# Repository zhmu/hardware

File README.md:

# hardware

Collection of various hardware projects

## avr-ldr

Simple PCB with an ATTiny2313 and PCA82C250 CAN <-> TTL transceiver to be able to monitor an energy meter's power LED.

## c64-psu

Commodore 64 power supply unit, intended to be safer, more reliable and more efficient than the original.

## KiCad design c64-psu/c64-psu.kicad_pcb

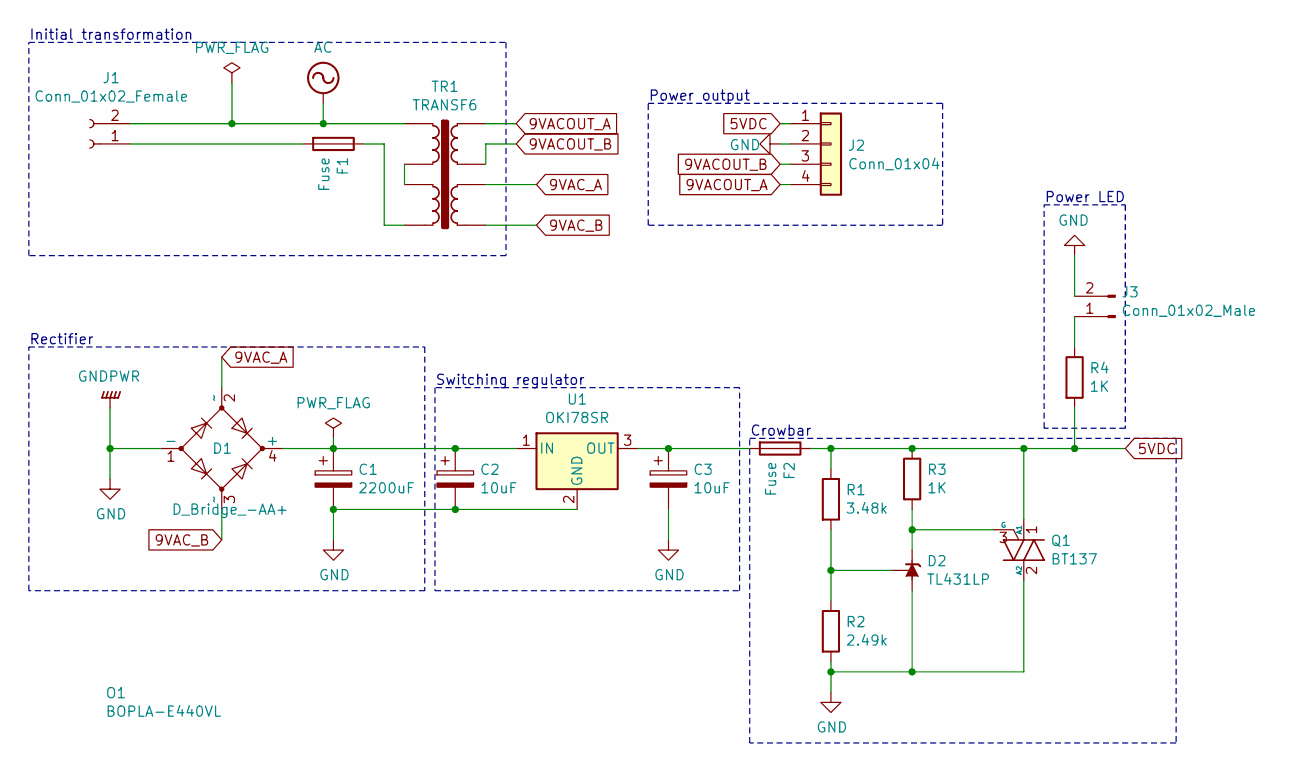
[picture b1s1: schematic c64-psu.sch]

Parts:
C1: 2200uF; CP_Radial_D13.0mm_P5.00mm
C2, C3: 10uF; CP_Radial_D5.0mm_P2.00mm
D1: D_Bridge_-AA+; Diode_Bridge_Vishay_KBU
D2: TL431LP; TO-92_HandSolder
F1, F2: Fuse; Fuseholder_Cylinder-5x20mm_Schurter_0031_8201_Horizontal_Op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
J1: Conn_01x02_Female; RND00023
J2: Conn_01x04; Molex_KK-396_A-41791-0004_1x04_P3.96mm_Vertical
J3: Conn_01x02_Male; Molex_KK-254_AE-6410-02A_1x02_P2.54mm_Vertical
O1: BOPLA-E440VL; BOPLA_E440VL
Q1: BT137; TO-220-3_Vertical
R1: 3.48k; R_Axial_DIN0207_L6.3mm_D2.5mm_P10.16mm_Horizontal
R2: 2.49k; R_Axial_DIN0207_L6.3mm_D2.5mm_P10.16mm_Horizontal
R3, R4: 1K; R_Axial_DIN0207_L6.3mm_D2.5mm_P10.16mm_Horizontal
TR1: TRANSF6; Transformer-FL30
U1: OKI78SR; TO-220-3_Vertical

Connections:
5VDC: F2.1, J2.1, Q1.1 (A1), R1.1, R3.1, R4.2
9VACOUT_A: J2.4, TR1.8
9VACOUT_B: J2.3, TR1.7
9VAC_A: D1.2 (~~), TR1.6
9VAC_B: D1.3 (~~), TR1.5
AC: J1.2, TR1.1
GND: C1.2, C2.2, C3.2, D1.1 (-), D2.2 (A), J2.2, J3.2, Q1.2 (A2), R2.2, U1.2 (GND)
unnamed: C1.1, C2.1, D1.4 (+), U1.1 (IN)
unnamed: C3.1, F2.2, U1.3 (OUT)
unnamed: D2.1 (REF), R1.2, R2.1
unnamed: D2.3 (K), Q1.3 (G), R3.2
unnamed: F1.1, TR1.4
unnamed: F1.2, J1.1
unnamed: J3.1, R4.1
unnamed: TR1.2, TR1.3

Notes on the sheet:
Initial transformation
Power output
Rectifier
Switching regulator
Crowbar
Power LED

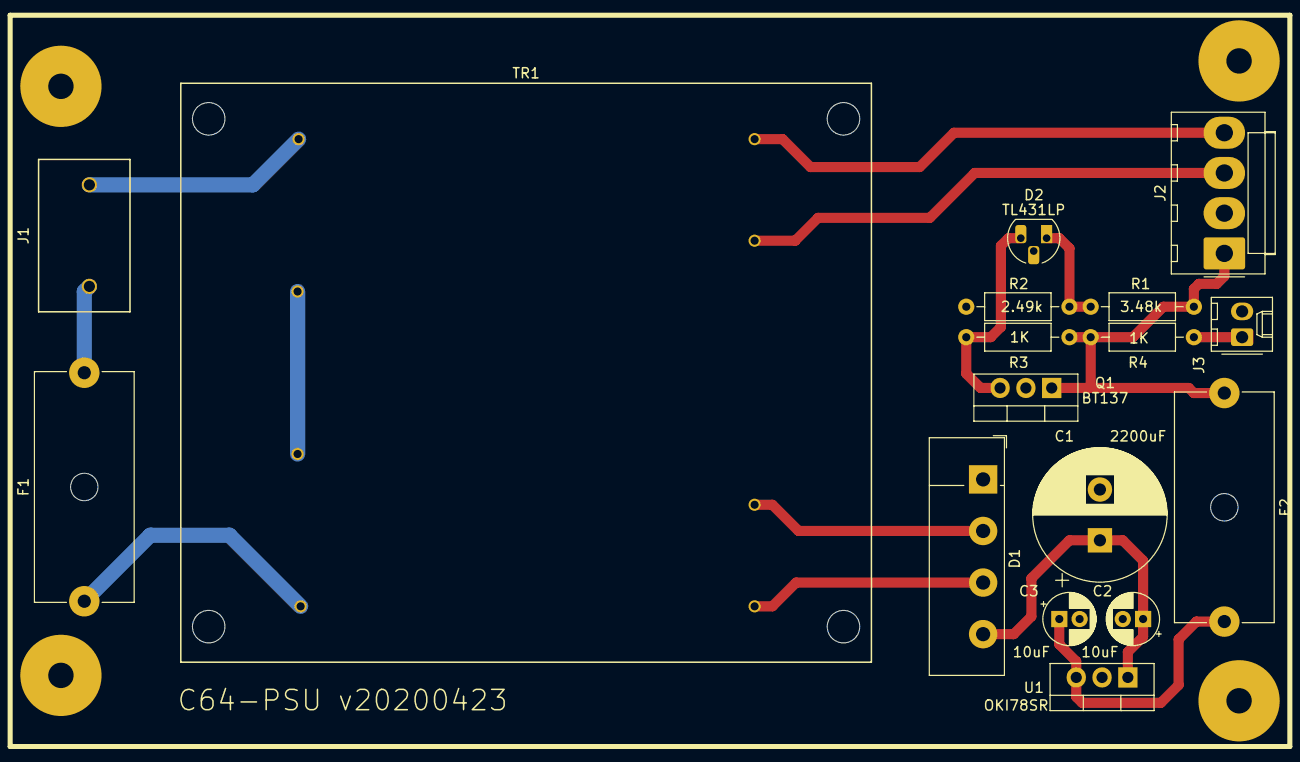
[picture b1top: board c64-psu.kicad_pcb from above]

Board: 2 copper layers, 18 parts (0 on the bottom side), 15 nets.

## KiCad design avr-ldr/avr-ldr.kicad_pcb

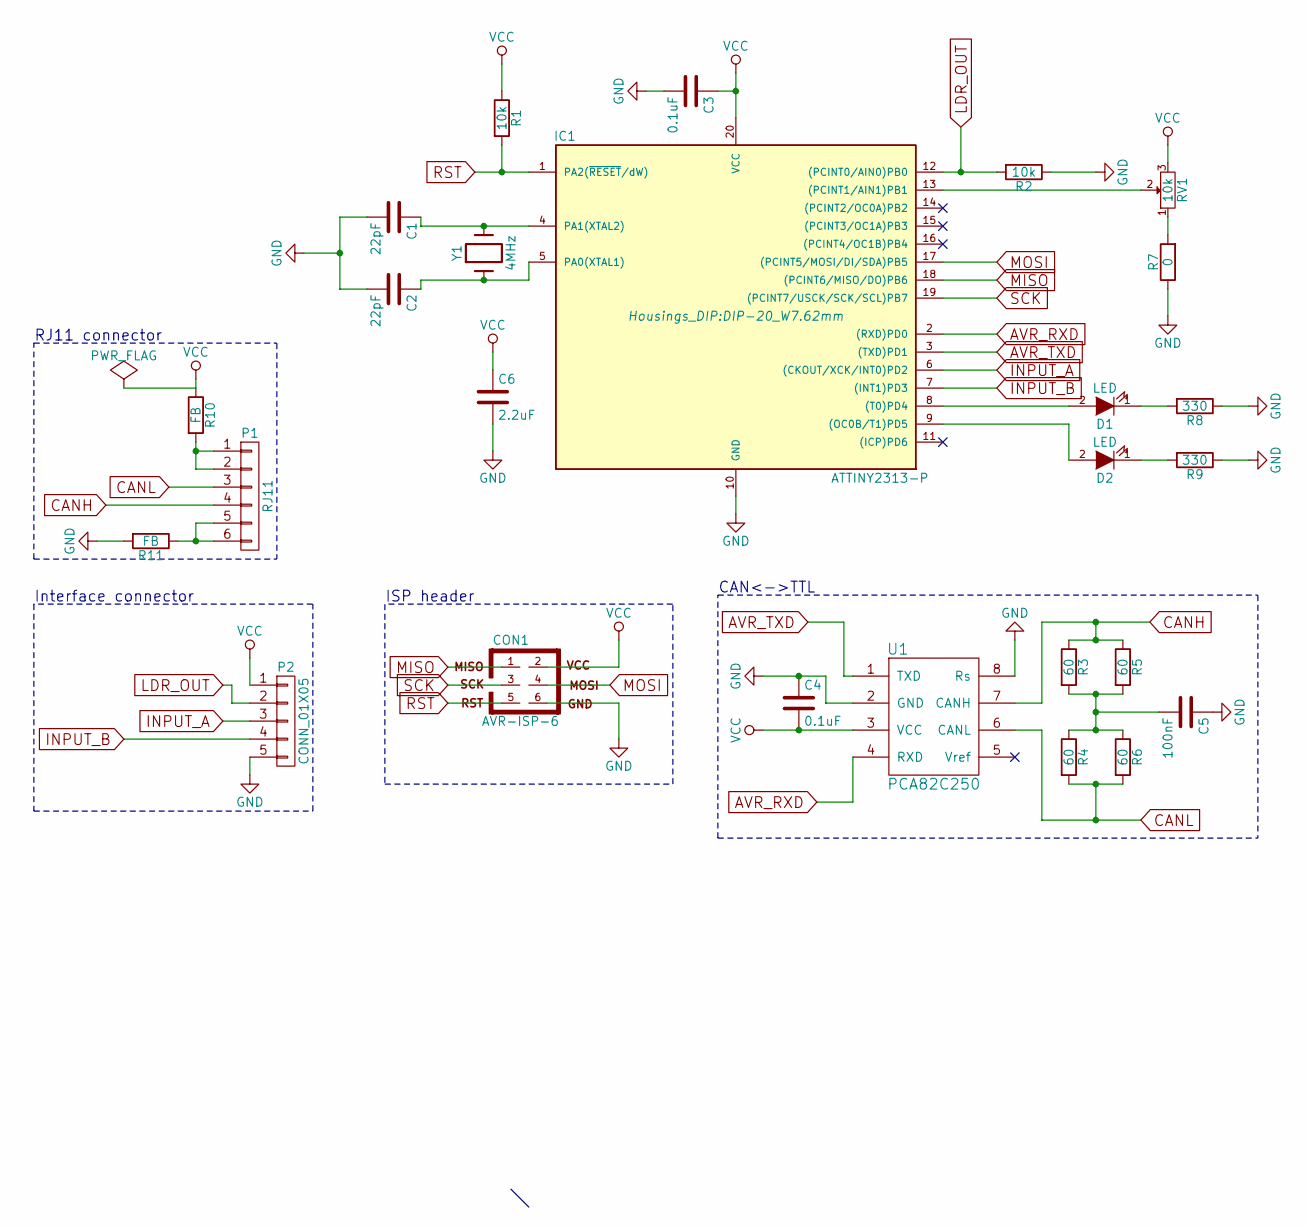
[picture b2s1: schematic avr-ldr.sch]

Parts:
C1, C2: 22pF; C_0603
C3, C4: 0.1uF; C_0603
C5: 100nF; C_0603
C6: 2.2uF; C_0603
CON1: AVR-ISP-6; Pin_Header_Straight_2x03
D1, D2: LED; LED_0603
IC1: ATTINY2313-P; DIP-20_W7.62mm
P1: RJ11; RJ11-6
P2: CONN_01X05; Pin_Header_Straight_1x05
R1, R2: 10k; R_0603
R3, R4, R5, R6: 60; R_0603
R7: 0; R_0603
R8, R9: 330; R_0603
R10, R11: FB; R_0603
RV1: 10k; Potentiometer_Triwood_RM-065
U1: PCA82C250; SOIC-8_3.9x4.9mm_Pitch1.27mm
Y1: 4MHz; Crystal_HC49-U_Vertical

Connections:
AVR_RXD: IC1.2 ((RXD)PD0), U1.4 (RXD)
AVR_TXD: IC1.3 ((TXD)PD1), U1.1 (TXD)
CANH: P1.4, R3.1, R5.1, U1.7 (CANH)
CANL: P1.3, R4.2, R6.2, U1.6 (CANL)
GND: C1.2, C2.2, C3.2, C4.1, C5.1, C6.2, CON1.6, IC1.10 (GND), P2.5, R2.1, R7.1, R8.1, R9.1, R11.2, U1.2 (GND), U1.8 (Rs)
INPUT_A: IC1.6 ((CKOUT/XCK/INT0)PD2), P2.3
INPUT_B: IC1.7 ((INT1)PD3), P2.4
LDR_OUT: IC1.12 ((PCINT0/AIN0)PB0), P2.2, R2.2
MISO: CON1.1, IC1.18 ((PCINT6/MISO/DO)PB6)
MOSI: CON1.4, IC1.17 ((PCINT5/MOSI/DI/SDA)PB5)
unnamed: C1.1, IC1.4 (PA1(XTAL2)), Y1.2
unnamed: C2.1, IC1.5 (PA0(XTAL1)), Y1.1
unnamed: C5.2, R3.2, R4.1, R5.2, R6.1
unnamed: D1.1 (K), R8.2
unnamed: D1.2 (A), IC1.8 ((T0)PD4)
unnamed: D2.1 (K), R9.2
unnamed: D2.2 (A), IC1.9 ((OC0B/T1)PD5)
unnamed: IC1.13 ((PCINT1/AIN1)PB1), RV1.2
unnamed: P1.1, P1.2, R10.2
unnamed: P1.5, P1.6, R11.1
unnamed: R7.2, RV1.1
RST: CON1.5, IC1.1 (PA2(~RESET~/dW)), R1.2
SCK: CON1.3, IC1.19 ((PCINT7/USCK/SCK/SCL)PB7)
VCC: C3.1, C4.2, C6.1, CON1.2, IC1.20 (VCC), P2.1, R1.1, R10.1, RV1.3, U1.3 (VCC)

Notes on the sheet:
CAN<->TTL
Interface connector
ISP header
RJ11 connector

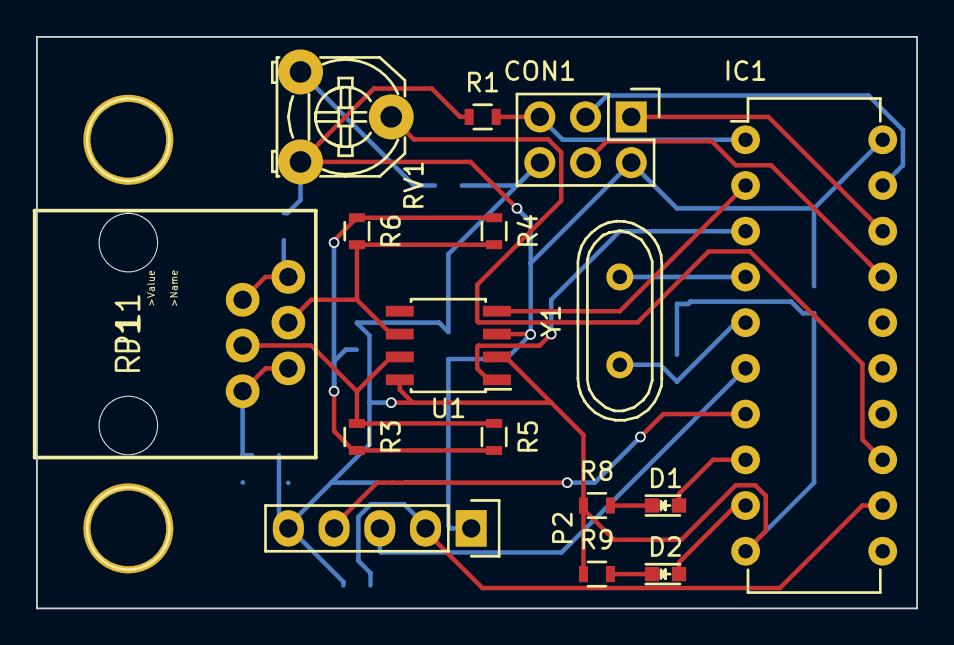
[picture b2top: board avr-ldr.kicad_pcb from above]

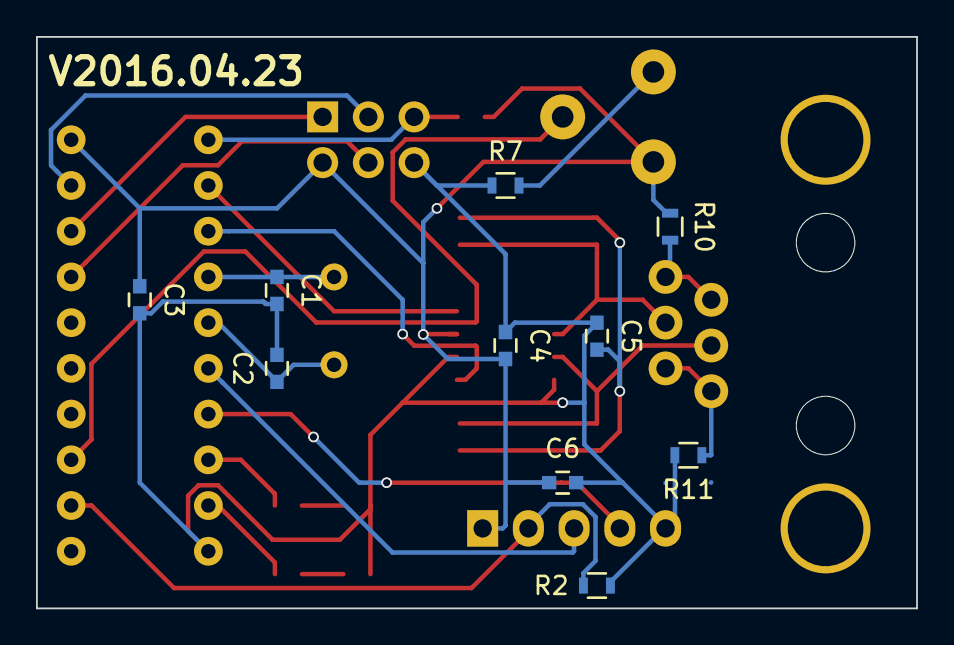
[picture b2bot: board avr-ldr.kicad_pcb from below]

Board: 2 copper layers, 48.9 x 31.8 mm, 26 parts (10 on the bottom side), 24 nets.

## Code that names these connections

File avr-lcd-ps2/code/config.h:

/**** Keyboard ***/
#define KBD_CLOCK		PD2
#define KBD_DATA		PD3

#define KBD_PORT_OUT		PORTD
#define KBD_PORT_IN		PIND
#define KBD_PORT_DIR		DDRD

/*** LCD ***/
#define LCD_RS_PORT	PORTD
#define LCD_RS_DIR	DDRD
#define LCD_RS		PD5

#define LCD_E_PORT	PORTB
#define LCD_E_DIR	DDRB
#define LCD_E0		PB0
#define LCD_E1		PB1

/*** LCD dimensions - 0x0 means the LCD is not present ***/
#define LCD_0_HEIGHT	4
#define LCD_0_WIDTH	20
#define LCD_1_HEIGHT	0
#define LCD_1_WIDTH	0

/* Multiplication value needed to get to the next row */
#define LCD_0_Y_MULTIPLIER	0x20
#define LCD_1_Y_MULTIPLIER	0x20

#define LCD_ALIGNMENT		HORIZONTAL

/* Size of the serial buffers */
#define SERIAL_BUFSIZE_RX	64
#define SERIAL_BUFSIZE_TX	32

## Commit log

2016-04-21 Import my AVR-LDR hardware project
2016-04-21 Ignore KiCad's temporary files, as stated in their documentation
2016-04-21 Add small blurp about my AVR-LDR project
2016-04-21 Add ferrite beads and correctly hook up the power flag
    It'll enter from the RJ-11 connector.
2016-04-23 First attempt at PCB layout
2016-04-27 Attempt #2 at my PCB design
    Guess I may actually create this one?!
2016-04-27 Add schematics of my AVR LED Matrix project
2016-05-03 Final changes to PCB (GND copper fill and date update)
    Off to OSHPark it has gone!
2016-05-03 Add AVR-LCD-PS/2 schematics which hooks 2x LCD + 1x PS/2 to RS-232 as a cheap console
2016-05-05 Add 4" LED digit clock project with an AVR and DS1307
2016-05-05 avr-lcd-ps2: Add the AVR code as well
2016-05-05 led-matrix: Add the (messy) code
2016-05-05 Move avr-clock schematics to kicad/
2016-05-05 avr-clock: Add (messy) code
2016-05-05 Add my serially-attached display+touchscreen for MusiXBoX
    This was a joint effort with Dwight Berendse, with valuable advice from Bart Bilos.
2016-05-05 avr-display-touch: Sync to a more recent version
2016-05-05 Add the 'status LCD display on server with AVR'-project code
    Schematics are trivial, but I may draw them if I can find the original design...
2016-05-06 Move schematics to kicad/
2016-05-06 Add energy measurement source code
2016-05-06 Move avr-ldr kicad/ stuff -> energy-measure
2016-05-06 rename avr-display-touch -> musixbox-ui because that is what it is
2016-05-06 avr-clock -> large-clock (the size is more important than the CPU)
2020-04-24 Add C64 power supply unit
    Special thanks to Bart Bilos for helping out!
2020-04-24 Update README blurb
2022-08-23 Add README.md, photos and schematics (PDF) to some projects
